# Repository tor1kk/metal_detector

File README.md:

# STM32 Based VLF Metal Detector Experiment(Ongoing)

## Introduction
The goal of this project is to develop a custom board with an STM32 microcontroller and utilize an existing commercial search coil. The working principle is as follows: a sinusoidal signal of a specific frequency is generated on the transmitting coil. The search coil is balanced so that in the absence of metal under it, the amplitude of the sinusoid on the receiving coil is minimal. If metal appears under the coil, the amplitude of the sinusoid on the receiving coil increases. The closer the metal or the larger the metal, the greater the amplitude. Additionally, it is possible to differentiate between metals by calculating the phase shift of the sinusoid on the receiving coil relative to the transmitting coil. This requires simultaneous reading of signals from both the transmitting and receiving coils, achieved using ADC dual regular simultaneous mode.

The information about the phase shift and the power of the received signal is displayed on the screen. In this project, LVGL was used to create the graphical interface.

## Project Overview
### Goals
The primary objective is to create a functioning metal detector using an STM32 microcontroller, with the capability to display signal data on a screen using LVGL. 

### Challenges
During the project, significant difficulties were encountered. When connecting the coil, the transmitted signal became distorted. This is likely due to an improperly designed matching circuit, although the exact cause was not determined. Any suggestions or ideas are welcome.

### Hardware
- **Microcontroller**: STM32H723ZGT6 was used to ensure sufficient processing power for rapid calculations. ADC1 and ADC2 were used in dual regular simultaneous mode to acquire signals from the coils. DAC was used to generate the signal for the coil and another DAC channel for sound generation.
- **Display**: A 2.8 inch display with an ILI9341 controller with a resistive touch screen on XPT2046 was used.
- **Schematic**: The schematic can be viewed in the `Hardware` folder in PDF format. [View Schematic](hardware/metal_detector_prototype.pdf)

### Software
- **Code**: The code related to this project is located in the `Program` folder.
- **Documentation**: The code is commented, and Doxygen documentation was generated. [View Doxygen Documentation](https://tor1kk.github.io/metal_detector/software/Program/Doc/html/index.html)

## Test Videos
### Working Test
A video demonstration of the working test can be found below: [View Test Video](media/test.mp4)

### Signal Distortion
A video showing the signal distortion when the coil is connected can be found below:[View Signal Distortion Video](media/signal_distortion.mp4)

## Images
### PCB Photo

## Conclusion
This project has been a valuable learning experience, despite the challenges faced. Further work is required to resolve the signal distortion issue and improve the overall performance of the metal detector.

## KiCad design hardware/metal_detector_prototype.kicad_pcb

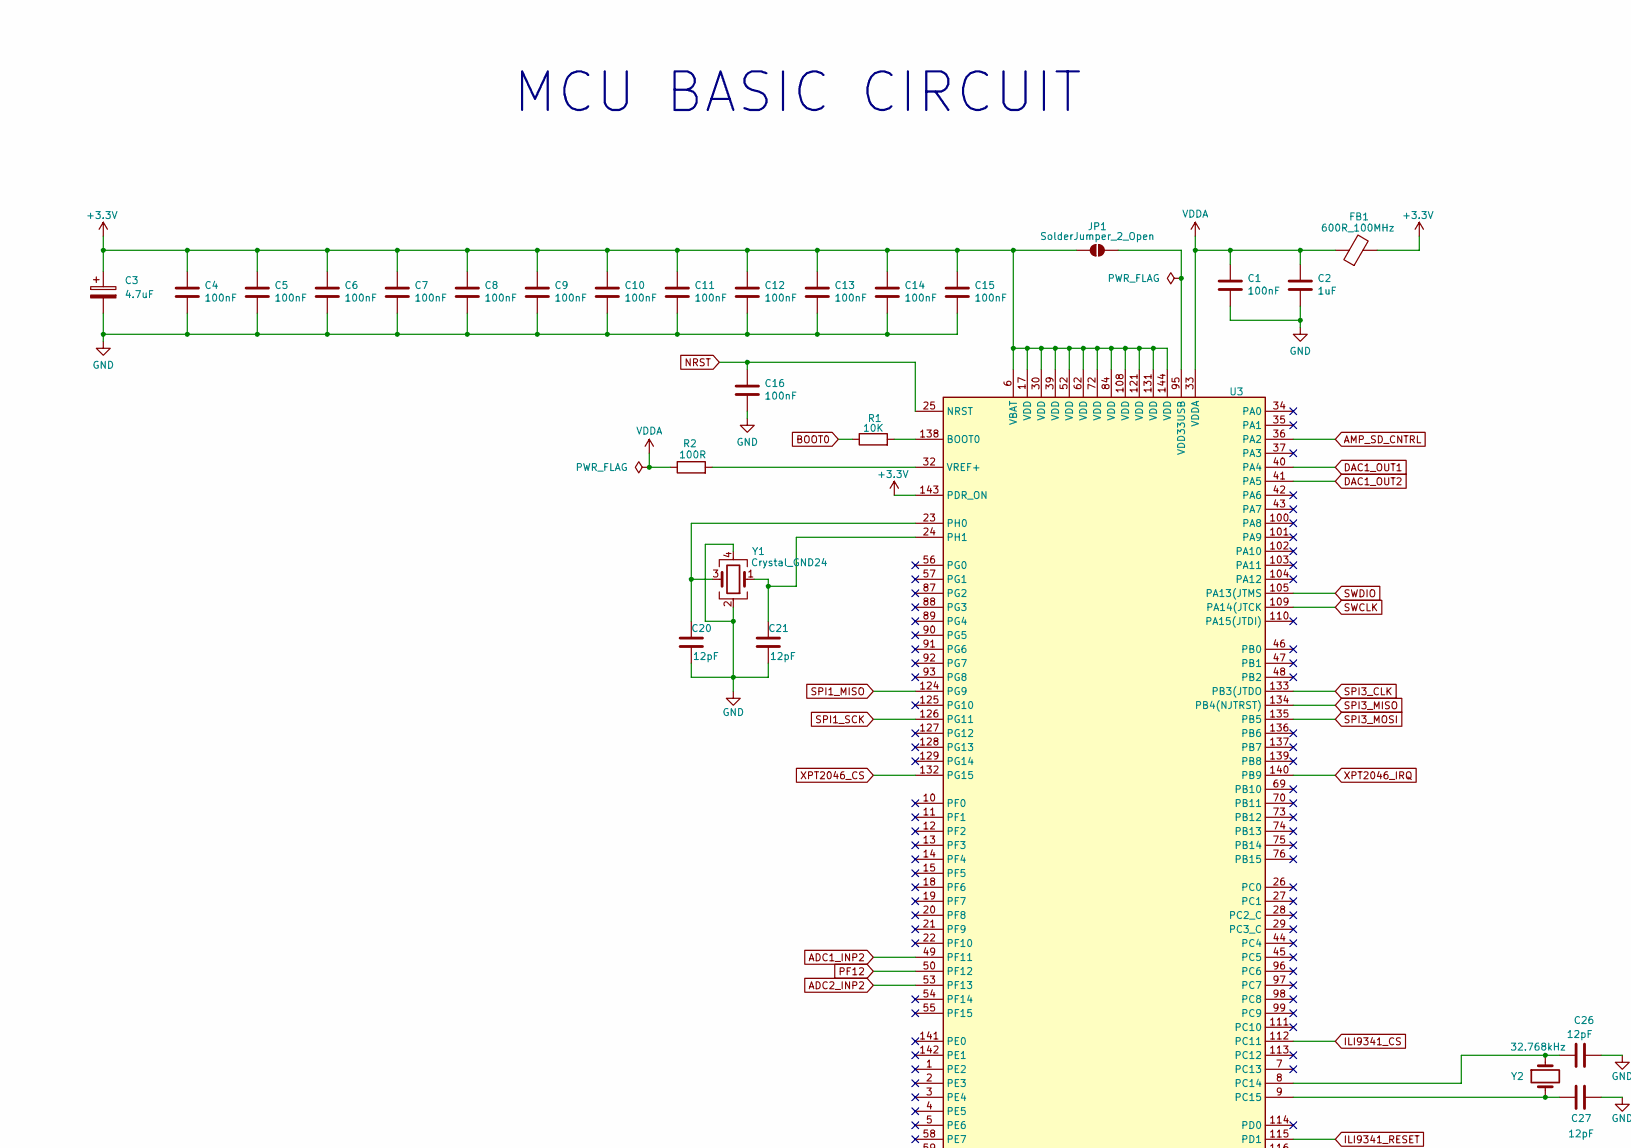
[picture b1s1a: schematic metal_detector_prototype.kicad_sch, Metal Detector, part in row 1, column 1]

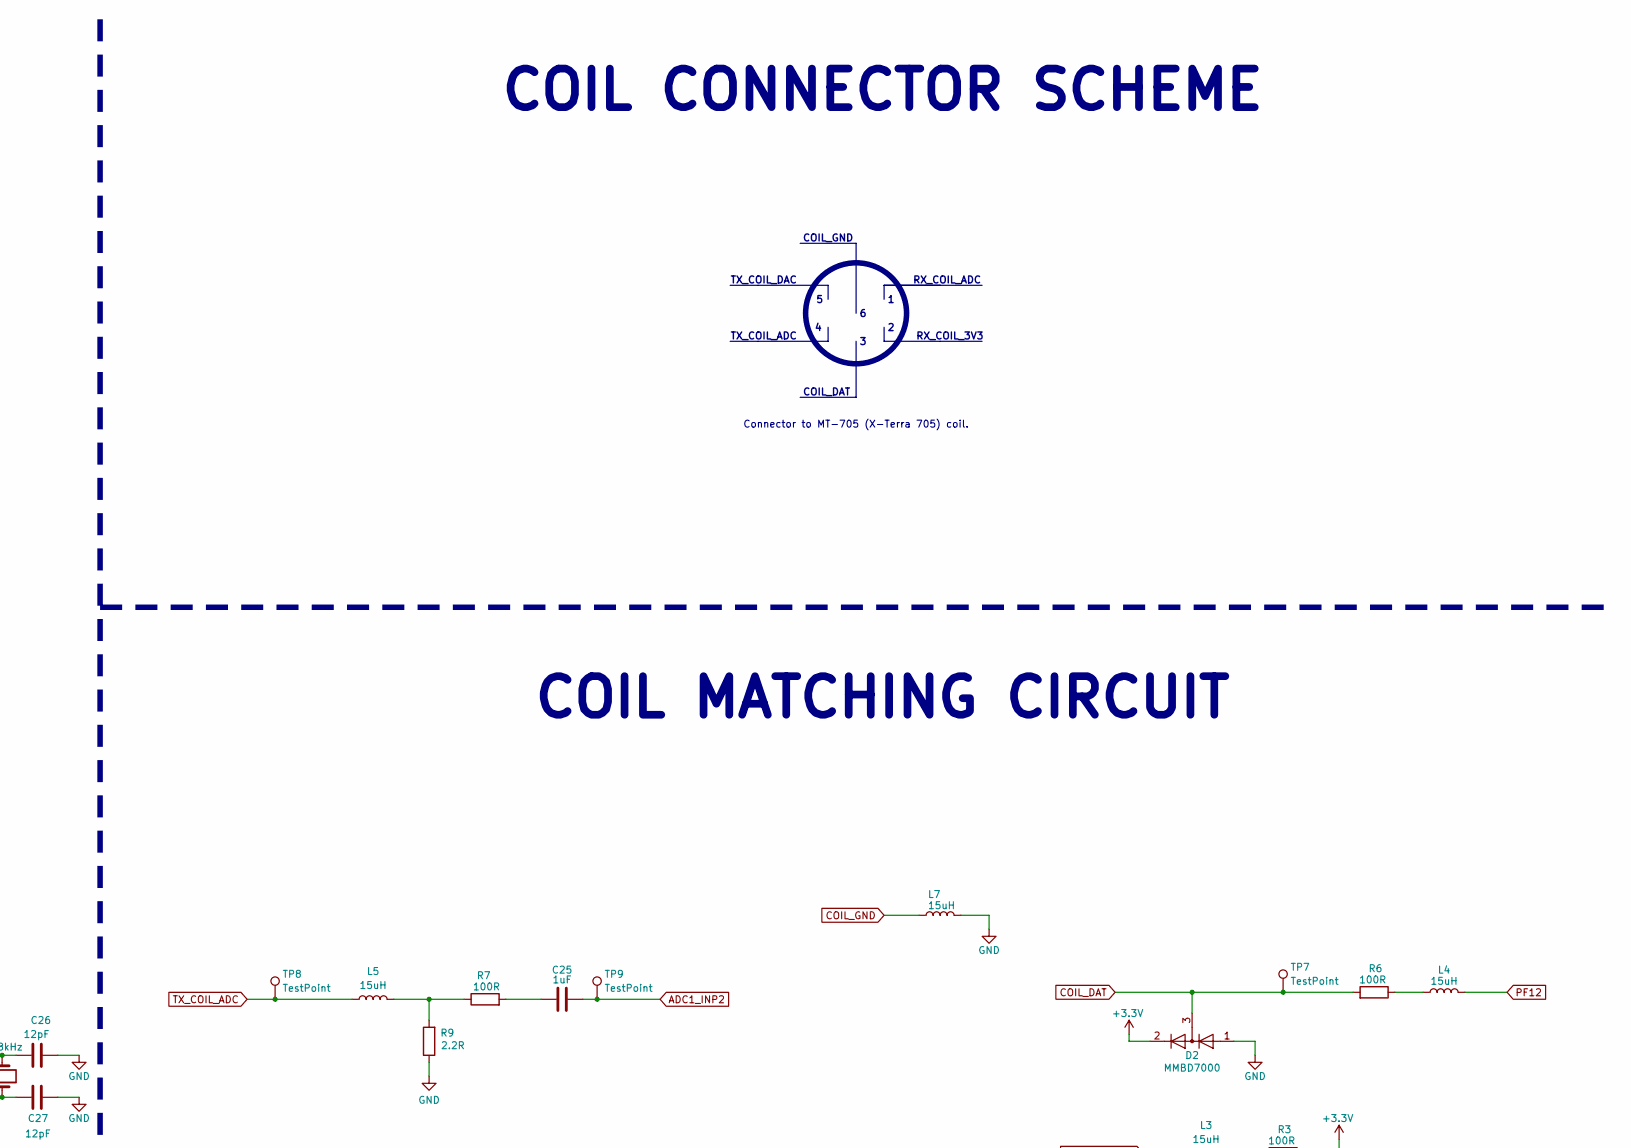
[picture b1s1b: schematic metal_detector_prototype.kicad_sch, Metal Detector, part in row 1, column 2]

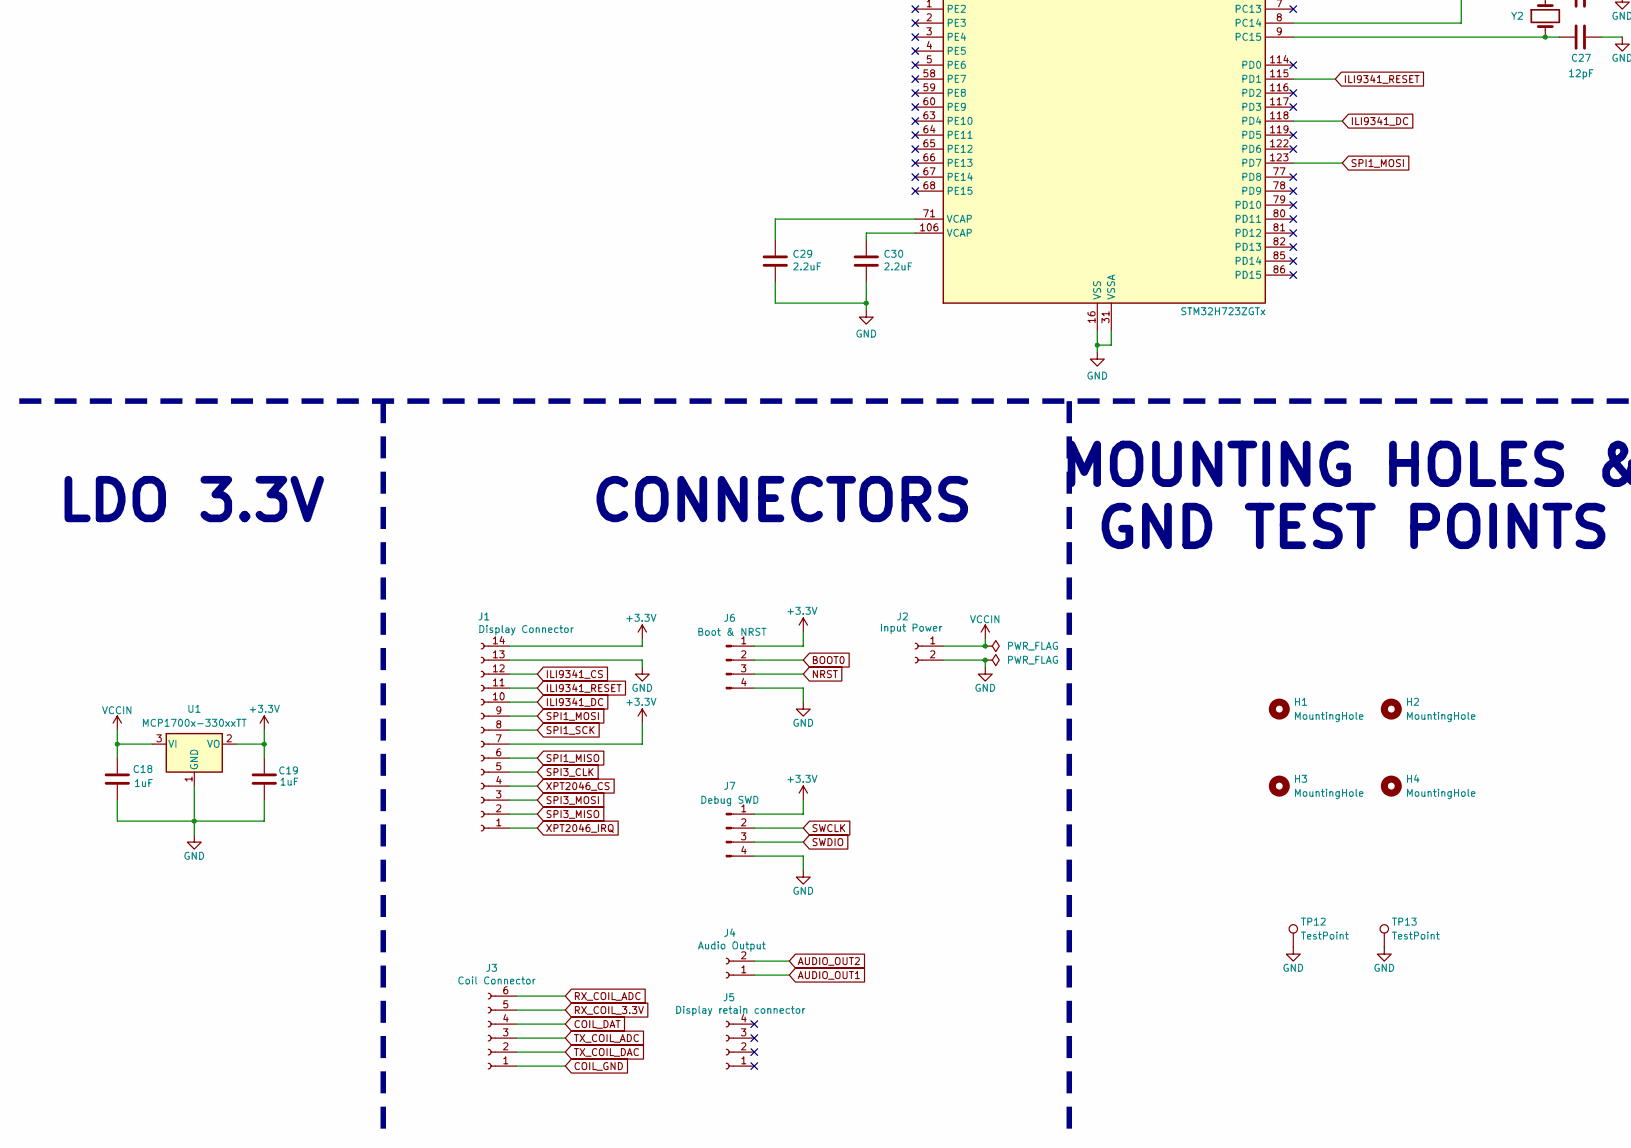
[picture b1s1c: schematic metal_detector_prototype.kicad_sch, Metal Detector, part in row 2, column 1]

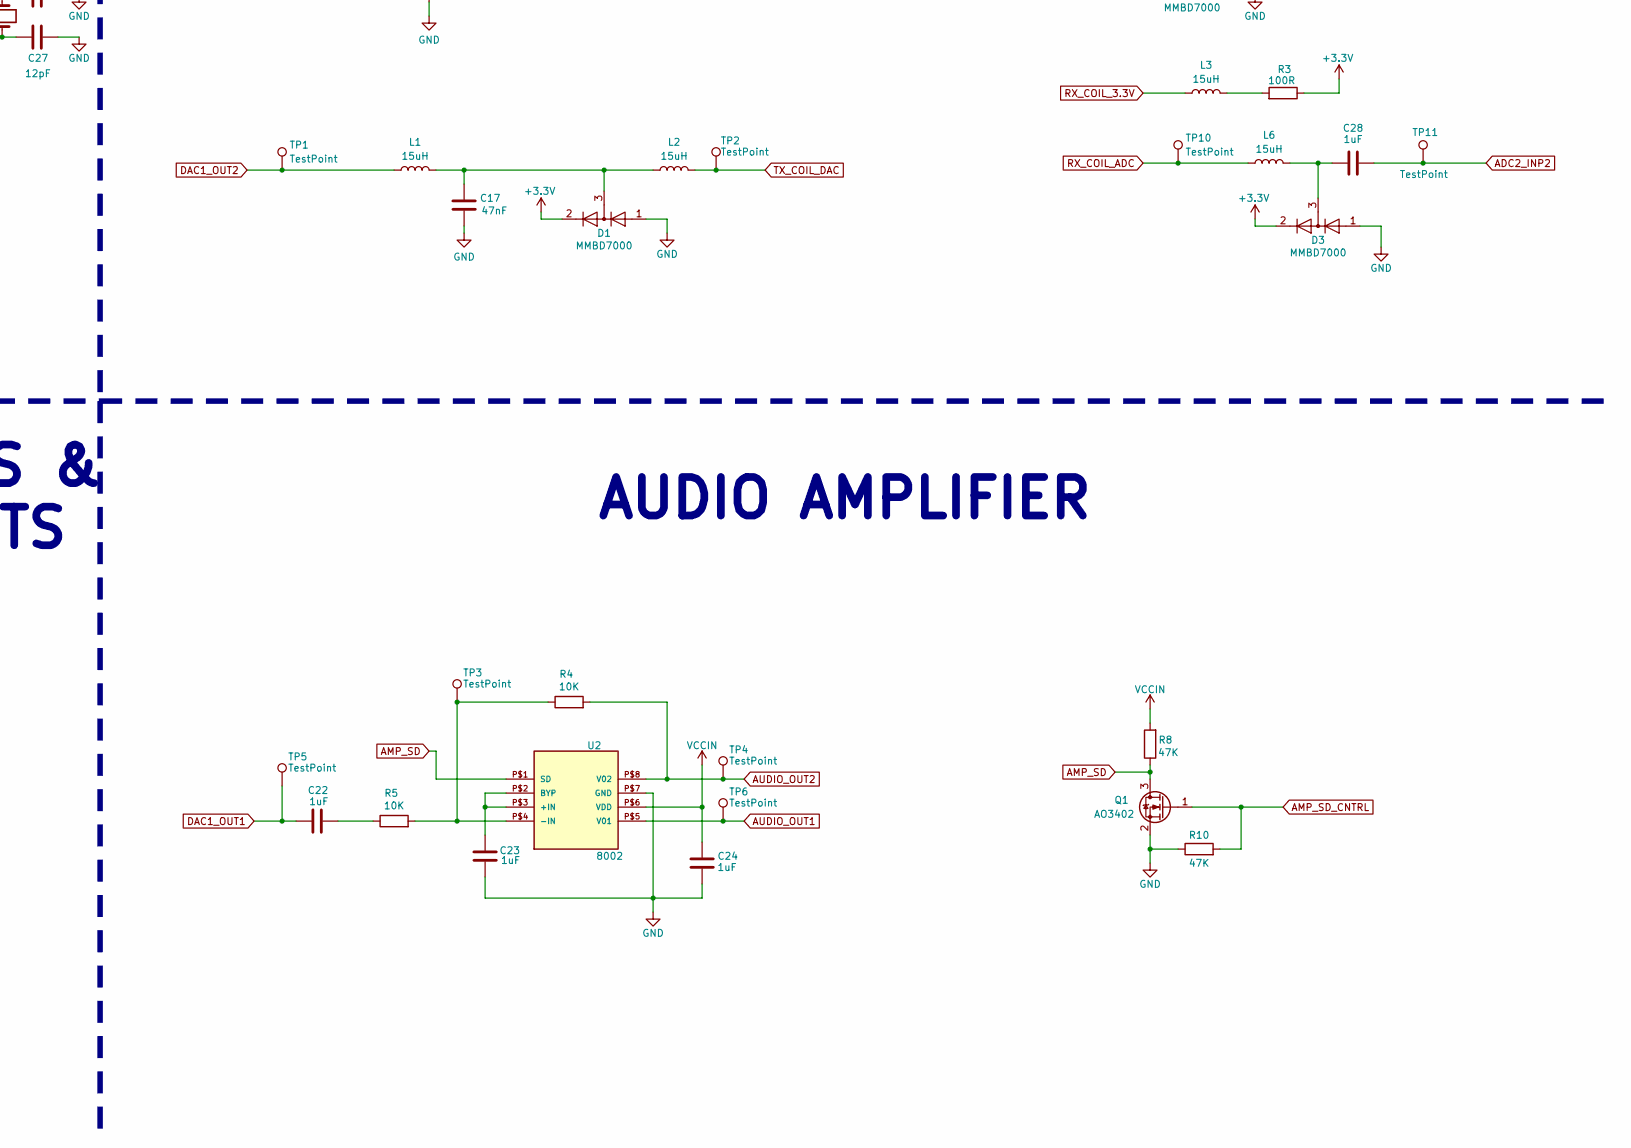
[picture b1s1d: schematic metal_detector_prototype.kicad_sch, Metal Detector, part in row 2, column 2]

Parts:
C1, C4, C5, C6, C7, C8, C9, C10, C11, C12, C13, C14, C15, C16: 100nF; C_0603_1608Metric
C2, C18, C19, C22, C23, C24, C25, C28: 1uF; C_0805_2012Metric
C3: 4.7uF; CP_EIA-3216-18_Kemet-A
C17: 47nF; C_0603_1608Metric
C20, C21, C26, C27: 12pF; C_0603_1608Metric
C29, C30: 2.2uF; C_0805_2012Metric
D1, D2, D3: MMBD7000; SOT-23
FB1: 600R_100MHz; R_0603_1608Metric
H1, H2, H3, H4: MountingHole; MountingHole_2.7mm_M2.5_ISO7380
J1: Display Connector; PinSocket_1x14_P2.54mm_Vertical
J2: Input Power; JST_XH_S2B-XH-A-1_1x02_P2.50mm_Horizontal
J3: Coil Connector; JST_XH_S6B-XH-A_1x06_P2.50mm_Horizontal
J4: Audio Output; JST_XH_S2B-XH-A_1x02_P2.50mm_Horizontal
J5: Display retain connector; PinSocket_1x06_P2.54mm_Vertical
J6: Boot & NRST; PinHeader_1x04_P2.54mm_Vertical
J7: Debug SWD; PinHeader_1x04_P2.54mm_Horizontal
JP1: SolderJumper_2_Open; SolderJumper-2_P1.3mm_Open_RoundedPad1.0x1.5mm
L1, L2, L3, L4, L5, L6, L7: 15uH; L_0603_1608Metric
Q1: AO3402; SOT-23
R1, R4, R5: 10K; R_0603_1608Metric
R2, R3, R6, R7: 100R; R_0603_1608Metric
R8, R10: 47K; R_0603_1608Metric
R9: 2.2R; R_0603_1608Metric
TP1, TP2, TP3, TP4, TP5, TP6, TP7, TP8, TP9, TP10, TP11, TP12, TP13: TestPoint; TestPoint_Loop_D1.80mm_Drill1.0mm_Beaded
U1: MCP1700x-330xxTT; SOT-23
U2: 8002; SOIC8
U3: STM32H723ZGTx; LQFP-144_20x20mm_P0.5mm
Y1: Crystal_GND24; Crystal_SMD_3225-4Pin_3.2x2.5mm
Y2: 32.768kHz; Crystal_SMD_3215-2Pin_3.2x1.5mm

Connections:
+3.3V: C3.1, C4.1, C5.1, C6.1, C7.1, C8.1, C9.1, C10.1, C11.1, C12.1, C13.1, C14.1, C15.1, C19.2, D1.2 (A), D2.2 (A), D3.2 (A), FB1.2, J1.7, J1.14, J6.1, J7.1, JP1.1 (A), R3.1, U1.2 (VO), U3.6 (VBAT), U3.17 (VDD), U3.30 (VDD), U3.39 (VDD), U3.52 (VDD), U3.62 (VDD), U3.72 (VDD), U3.84 (VDD), U3.108 (VDD), U3.121 (VDD), U3.131 (VDD), U3.143 (PDR_ON), U3.144 (VDD)
ADC1_INP2: C25.2, TP9.1, U3.49 (PF11)
ADC2_INP2: C28.2, TP11.1, U3.53 (PF13)
AMP_SD: Q1.3 (D), R8.1, U2.P$1 (SD)
AMP_SD_CNTRL: Q1.1 (G), R10.2, U3.36 (PA2)
AUDIO_OUT1: J4.1, TP6.1, U2.P$5 (V01)
AUDIO_OUT2: J4.2, R4.2, TP4.1, U2.P$8 (V02)
BOOT0: J6.2, R1.1
COIL_DAT: D2.3 (K), J3.4, R6.2, TP7.1
COIL_GND: J3.1, L7.1
DAC1_OUT1: C22.2, TP5.1, U3.40 (PA4)
DAC1_OUT2: L1.1, TP1.1, U3.41 (PA5)
GND: C1.2, C2.2, C3.2, C4.2, C5.2, C6.2, C7.2, C8.2, C9.2, C10.2, C11.2, C12.2, C13.2, C14.2, C15.2, C16.2, C17.2, C18.1, C19.1, C20.1, C21.1, C23.2, C24.1, C26.1, C27.1, C29.2, C30.2, D1.1 (K), D2.1 (K), D3.1 (K), J1.13, J2.2, J6.4, J7.4, L7.2, Q1.2 (S), R9.1, R10.1, TP12.1, TP13.1, U1.1 (GND), U2.P$7 (GND), U3.16 (VSS), U3.31 (VSSA), U3.38 (VSS), U3.51 (VSS), U3.61 (VSS), U3.83 (VSS), U3.94 (VSS), U3.107 (VSS), U3.120 (VSS), U3.130 (VSS), Y1.2, Y1.4
ILI9341_CS: J1.12, U3.112 (PC11)
ILI9341_DC: J1.10, U3.118 (PD4)
ILI9341_RESET: J1.11, U3.115 (PD1)
NRST: C16.1, J6.3, U3.25 (NRST)
unnamed: C17.1, D1.3 (K), L1.2, L2.1
unnamed: C22.1, R5.1
unnamed: C25.1, R7.2
unnamed: C28.1, D3.3 (K), L6.2
unnamed: C29.1, U3.71 (VCAP)
unnamed: C30.1, U3.106 (VCAP)
unnamed: JP1.2 (B), U3.95 (VDD33USB)
unnamed: L3.1, R3.2
unnamed: L4.2, R6.1
unnamed: L5.2, R7.1, R9.2
unnamed: C23.1, U2.P$2 (BYP), U2.P$3 (+IN)
unnamed: R4.1, R5.2, TP3.1, U2.P$4 (-IN)
unnamed: R1.2, U3.138 (BOOT0)
unnamed: C26.2, U3.8 (PC14), Y2.1
unnamed: C27.2, U3.9 (PC15), Y2.2
unnamed: C20.2, U3.23 (PH0), Y1.3
unnamed: C21.2, U3.24 (PH1), Y1.1
unnamed: R2.2, U3.32 (VREF+)
PF12: L4.1, U3.50 (PF12)
RX_COIL_3.3V: J3.5, L3.2
RX_COIL_ADC: J3.6, L6.1, TP10.1
SPI1_MISO: J1.6, U3.124 (PG9)
SPI1_MOSI: J1.9, U3.123 (PD7)
SPI1_SCK: J1.8, U3.126 (PG11)
SPI3_CLK: J1.5, U3.133 (PB3(JTDO)
SPI3_MISO: J1.2, U3.134 (PB4(NJTRST))
SPI3_MOSI: J1.3, U3.135 (PB5)
SWCLK: J7.2, U3.109 (PA14(JTCK)
SWDIO: J7.3, U3.105 (PA13(JTMS)
TX_COIL_ADC: J3.3, L5.1, TP8.1
TX_COIL_DAC: J3.2, L2.2, TP2.1
VCCIN: C18.2, C24.2, J2.1, R8.2, U1.3 (VI), U2.P$6 (VDD)
VDDA: C1.1, C2.1, FB1.1, R2.1, U3.33 (VDDA)
XPT2046_CS: J1.4, U3.132 (PG15)
XPT2046_IRQ: J1.1, U3.140 (PB9)

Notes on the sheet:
COIL MATCHING CIRCUIT
TX_COIL_DAC
COIL_GND
AUDIO AMPLIFIER
COIL CONNECTOR SCHEME
RX_COIL_3V3
RX_COIL_ADC
COIL_DAT
TX_COIL_ADC
MCU BASIC CIRCUIT
CONNECTORS
Connector to MT-705 (X-Terra 705) coil.
MOUNTING HOLES & GND TEST POINTS
LDO 3.3V

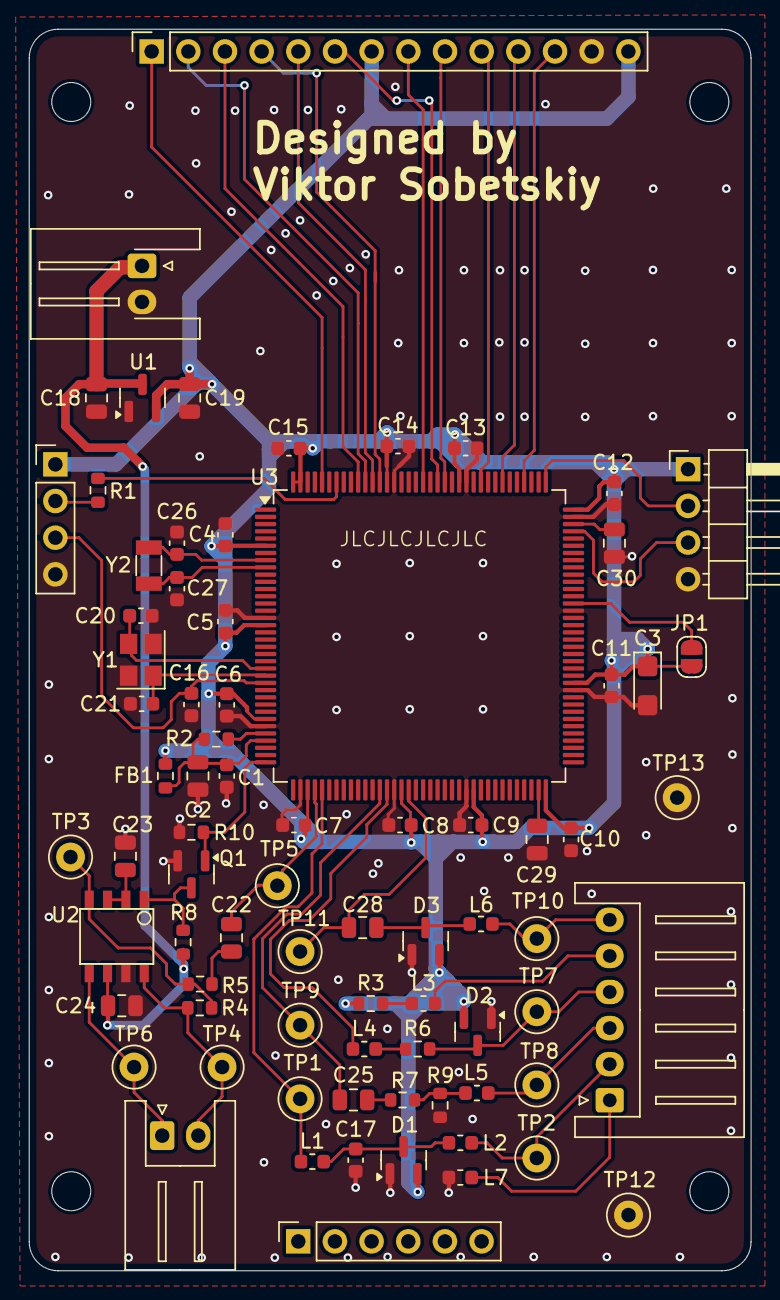
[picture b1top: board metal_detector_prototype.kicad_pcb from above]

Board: 4 copper layers, 50.0 x 86.0 mm, 82 parts (0 on the bottom side), 52 nets.

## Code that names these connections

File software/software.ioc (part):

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Mcu.Name=STM32H723ZGTx
Mcu.Package=LQFP144
Mcu.UserName=STM32H723ZGTx
PA13(JTMS/SWDIO).Mode=Serial_Wire
PA13(JTMS/SWDIO).Signal=DEBUG_JTMS-SWDIO
PA14(JTCK/SWCLK).Mode=Serial_Wire
PA14(JTCK/SWCLK).Signal=DEBUG_JTCK-SWCLK
PA2.GPIOParameters=PinState,GPIO_Label
PA2.GPIO_Label=AMP_SD_CNTRL
PA2.PinState=GPIO_PIN_RESET
PA2.Signal=GPIO_Output
PA4.Signal=COMP_DAC11_group
PA5.Signal=COMP_DAC12_group
PB3(JTDO/TRACESWO).Mode=Full_Duplex_Master
PB3(JTDO/TRACESWO).Signal=SPI3_SCK
PB4(NJTRST).Mode=Full_Duplex_Master
PB4(NJTRST).Signal=SPI3_MISO
PB5.Mode=Full_Duplex_Master
PB5.Signal=SPI3_MOSI
PB9.GPIOParameters=GPIO_PuPd,GPIO_Label
PB9.GPIO_Label=XPT2046_IRQ
PB9.GPIO_PuPd=GPIO_PULLUP
PB9.Signal=GPIO_Input
PC11.GPIOParameters=PinState,GPIO_Label
PC11.GPIO_Label=ILI9341_CS
PC11.PinState=GPIO_PIN_SET
PC11.Signal=GPIO_Output
PC14-OSC32_IN.Mode=LSE-External-Oscillator
PC14-OSC32_IN.Signal=RCC_OSC32_IN
PC15-OSC32_OUT.Mode=LSE-External-Oscillator
PC15-OSC32_OUT.Signal=RCC_OSC32_OUT
PD1.GPIOParameters=PinState,GPIO_Label
PD1.GPIO_Label=ILI9341_RESET
PD1.PinState=GPIO_PIN_SET
PD1.Signal=GPIO_Output
PD4.GPIOParameters=PinState,GPIO_Label
PD4.GPIO_Label=ILI9341_DC
PD4.PinState=GPIO_PIN_SET
PD4.Signal=GPIO_Output
PD7.Mode=Full_Duplex_Master
PD7.Signal=SPI1_MOSI
PF11.Mode=IN2-Single-Ended
PF11.Signal=ADC1_INP2
PF12.GPIOParameters=GPIO_Speed,GPIO_Label
PF12.GPIO_Label=COIL_DAT
PF12.GPIO_Speed=GPIO_SPEED_FREQ_VERY_HIGH
PF12.Signal=GPIO_Output
PF13.Mode=IN2-Single-Ended
PF13.Signal=ADC2_INP2
PG11.Mode=Full_Duplex_Master
PG11.Signal=SPI1_SCK
PG15.GPIOParameters=PinState,GPIO_Label
PG15.GPIO_Label=XPT2046_CS
PG15.PinState=GPIO_PIN_SET
PG15.Signal=GPIO_Output
PG9.Mode=Full_Duplex_Master
PG9.Signal=SPI1_MISO
PH0-OSC_IN.Mode=HSE-External-Oscillator
PH0-OSC_IN.Signal=RCC_OSC_IN
PH1-OSC_OUT.Mode=HSE-External-Oscillator
PH1-OSC_OUT.Signal=RCC_OSC_OUT
RCC.SYSCLKFreq_VALUE=550000000
RCC.SYSCLKSource=RCC_SYSCLKSOURCE_PLLCLK
board=custom

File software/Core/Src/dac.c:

/* USER CODE BEGIN Header */
/**
  ******************************************************************************
  * @file    dac.c
  * @brief   This file provides code for the configuration
  *          of the DAC instances.
  ******************************************************************************
  * @attention
  *
  * Copyright (c) 2024 STMicroelectronics.
  * All rights reserved.
  *
  * This software is licensed under terms that can be found in the LICENSE file
  * in the root directory of this software component.
  * If no LICENSE file comes with this software, it is provided AS-IS.
  *
  ******************************************************************************
  */
/* USER CODE END Header */
/* Includes ------------------------------------------------------------------*/
#include "dac.h"

/* USER CODE BEGIN 0 */

/* USER CODE END 0 */

DAC_HandleTypeDef hdac1;
DMA_HandleTypeDef hdma_dac1_ch1;
DMA_HandleTypeDef hdma_dac1_ch2;

/* DAC1 init function */
void MX_DAC1_Init(void)
{

  /* USER CODE BEGIN DAC1_Init 0 */

  /* USER CODE END DAC1_Init 0 */

  DAC_ChannelConfTypeDef sConfig = {0};

  /* USER CODE BEGIN DAC1_Init 1 */

  /* USER CODE END DAC1_Init 1 */

  /** DAC Initialization
  */
  hdac1.Instance = DAC1;
  if (HAL_DAC_Init(&hdac1) != HAL_OK)
  {
    Error_Handler();
  }

  /** DAC channel OUT1 config
  */
  sConfig.DAC_SampleAndHold = DAC_SAMPLEANDHOLD_DISABLE;
  sConfig.DAC_Trigger = DAC_TRIGGER_T2_TRGO;
  sConfig.DAC_OutputBuffer = DAC_OUTPUTBUFFER_ENABLE;
  sConfig.DAC_ConnectOnChipPeripheral = DAC_CHIPCONNECT_DISABLE;
  sConfig.DAC_UserTrimming = DAC_TRIMMING_FACTORY;
  if (HAL_DAC_ConfigChannel(&hdac1, &sConfig, DAC_CHANNEL_1) != HAL_OK)
  {
    Error_Handler();
  }

  /** DAC channel OUT2 config
  */
  if (HAL_DAC_ConfigChannel(&hdac1, &sConfig, DAC_CHANNEL_2) != HAL_OK)
  {
    Error_Handler();
  }
  /* USER CODE BEGIN DAC1_Init 2 */

  /* USER CODE END DAC1_Init 2 */

}

void HAL_DAC_MspInit(DAC_HandleTypeDef* dacHandle)
{

  GPIO_InitTypeDef GPIO_InitStruct = {0};
  if(dacHandle->Instance==DAC1)
  {
  /* USER CODE BEGIN DAC1_MspInit 0 */

  /* USER CODE END DAC1_MspInit 0 */
    /* DAC1 clock enable */
    __HAL_RCC_DAC12_CLK_ENABLE();

    __HAL_RCC_GPIOA_CLK_ENABLE();
    /**DAC1 GPIO Configuration
    PA4     ------> DAC1_OUT1
    PA5     ------> DAC1_OUT2
    */
    GPIO_InitStruct.Pin = GPIO_PIN_4|GPIO_PIN_5;
    GPIO_InitStruct.Mode = GPIO_MODE_ANALOG;
    GPIO_InitStruct.Pull = GPIO_NOPULL;
    HAL_GPIO_Init(GPIOA, &GPIO_InitStruct);

    /* DAC1 DMA Init */
    /* DAC1_CH1 Init */
    hdma_dac1_ch1.Instance = DMA1_Stream0;
    hdma_dac1_ch1.Init.Request = DMA_REQUEST_DAC1;
    hdma_dac1_ch1.Init.Direction = DMA_MEMORY_TO_PERIPH;
    hdma_dac1_ch1.Init.PeriphInc = DMA_PINC_DISABLE;
    hdma_dac1_ch1.Init.MemInc = DMA_MINC_ENABLE;
    hdma_dac1_ch1.Init.PeriphDataAlignment = DMA_PDATAALIGN_WORD;
    hdma_dac1_ch1.Init.MemDataAlignment = DMA_MDATAALIGN_WORD;
    hdma_dac1_ch1.Init.Mode = DMA_CIRCULAR;
    hdma_dac1_ch1.Init.Priority = DMA_PRIORITY_LOW;
    hdma_dac1_ch1.Init.FIFOMode = DMA_FIFOMODE_DISABLE;
    if (HAL_DMA_Init(&hdma_dac1_ch1) != HAL_OK)
    {
      Error_Handler();
    }

    __HAL_LINKDMA(dacHandle,DMA_Handle1,hdma_dac1_ch1);

    /* DAC1_CH2 Init */
    hdma_dac1_ch2.Instance = DMA1_Stream3;
    hdma_dac1_ch2.Init.Request = DMA_REQUEST_DAC2;
    hdma_dac1_ch2.Init.Direction = DMA_MEMORY_TO_PERIPH;
    hdma_dac1_ch2.Init.PeriphInc = DMA_PINC_DISABLE;
    hdma_dac1_ch2.Init.MemInc = DMA_MINC_ENABLE;
    hdma_dac1_ch2.Init.PeriphDataAlignment = DMA_PDATAALIGN_WORD;
    hdma_dac1_ch2.Init.MemDataAlignment = DMA_MDATAALIGN_WORD;
    hdma_dac1_ch2.Init.Mode = DMA_CIRCULAR;
    hdma_dac1_ch2.Init.Priority = DMA_PRIORITY_LOW;
    hdma_dac1_ch2.Init.FIFOMode = DMA_FIFOMODE_DISABLE;
    if (HAL_DMA_Init(&hdma_dac1_ch2) != HAL_OK)
    {
      Error_Handler();
    }

    __HAL_LINKDMA(dacHandle,DMA_Handle2,hdma_dac1_ch2);

  /* USER CODE BEGIN DAC1_MspInit 1 */

  /* USER CODE END DAC1_MspInit 1 */
  }
}

void HAL_DAC_MspDeInit(DAC_HandleTypeDef* dacHandle)
{

  if(dacHandle->Instance==DAC1)
  {
  /* USER CODE BEGIN DAC1_MspDeInit 0 */

  /* USER CODE END DAC1_MspDeInit 0 */
    /* Peripheral clock disable */
    __HAL_RCC_DAC12_CLK_DISABLE();

    /**DAC1 GPIO Configuration
    PA4     ------> DAC1_OUT1
    PA5     ------> DAC1_OUT2
    */
    HAL_GPIO_DeInit(GPIOA, GPIO_PIN_4|GPIO_PIN_5);

    /* DAC1 DMA DeInit */
    HAL_DMA_DeInit(dacHandle->DMA_Handle1);
    HAL_DMA_DeInit(dacHandle->DMA_Handle2);
  /* USER CODE BEGIN DAC1_MspDeInit 1 */

  /* USER CODE END DAC1_MspDeInit 1 */
  }
}

/* USER CODE BEGIN 1 */

/* USER CODE END 1 */

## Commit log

2024-08-05 Links fix
2024-08-07 Create LICENSE
